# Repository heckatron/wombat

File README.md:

# wombat
Wireless sensor network using MQTT

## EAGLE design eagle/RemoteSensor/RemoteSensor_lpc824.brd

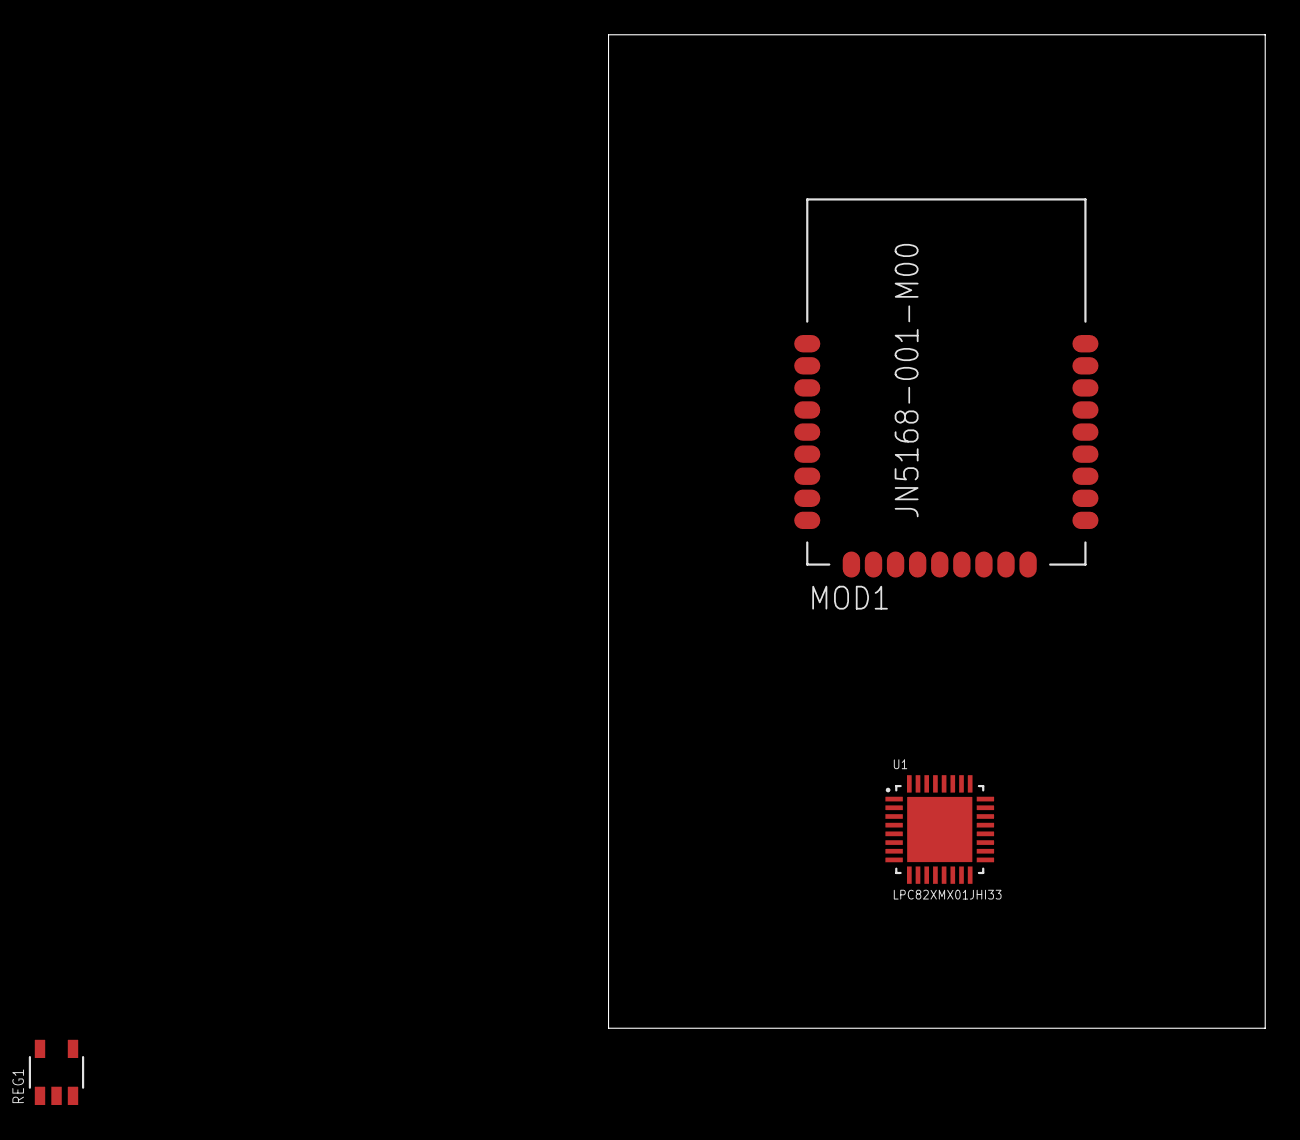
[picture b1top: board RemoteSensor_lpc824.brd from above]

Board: 2 copper layers, 37.8 x 57.1 mm, 3 parts (0 on the bottom side), 2 nets, no tracks yet.

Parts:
MOD1: JN5168-001-M00
REG1: LP3985DBV; SOT23
U1: LPC82XMX01JHI33; QFN33

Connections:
GND: MOD1.18, REG1.2
VDD: MOD1.17, U1.19

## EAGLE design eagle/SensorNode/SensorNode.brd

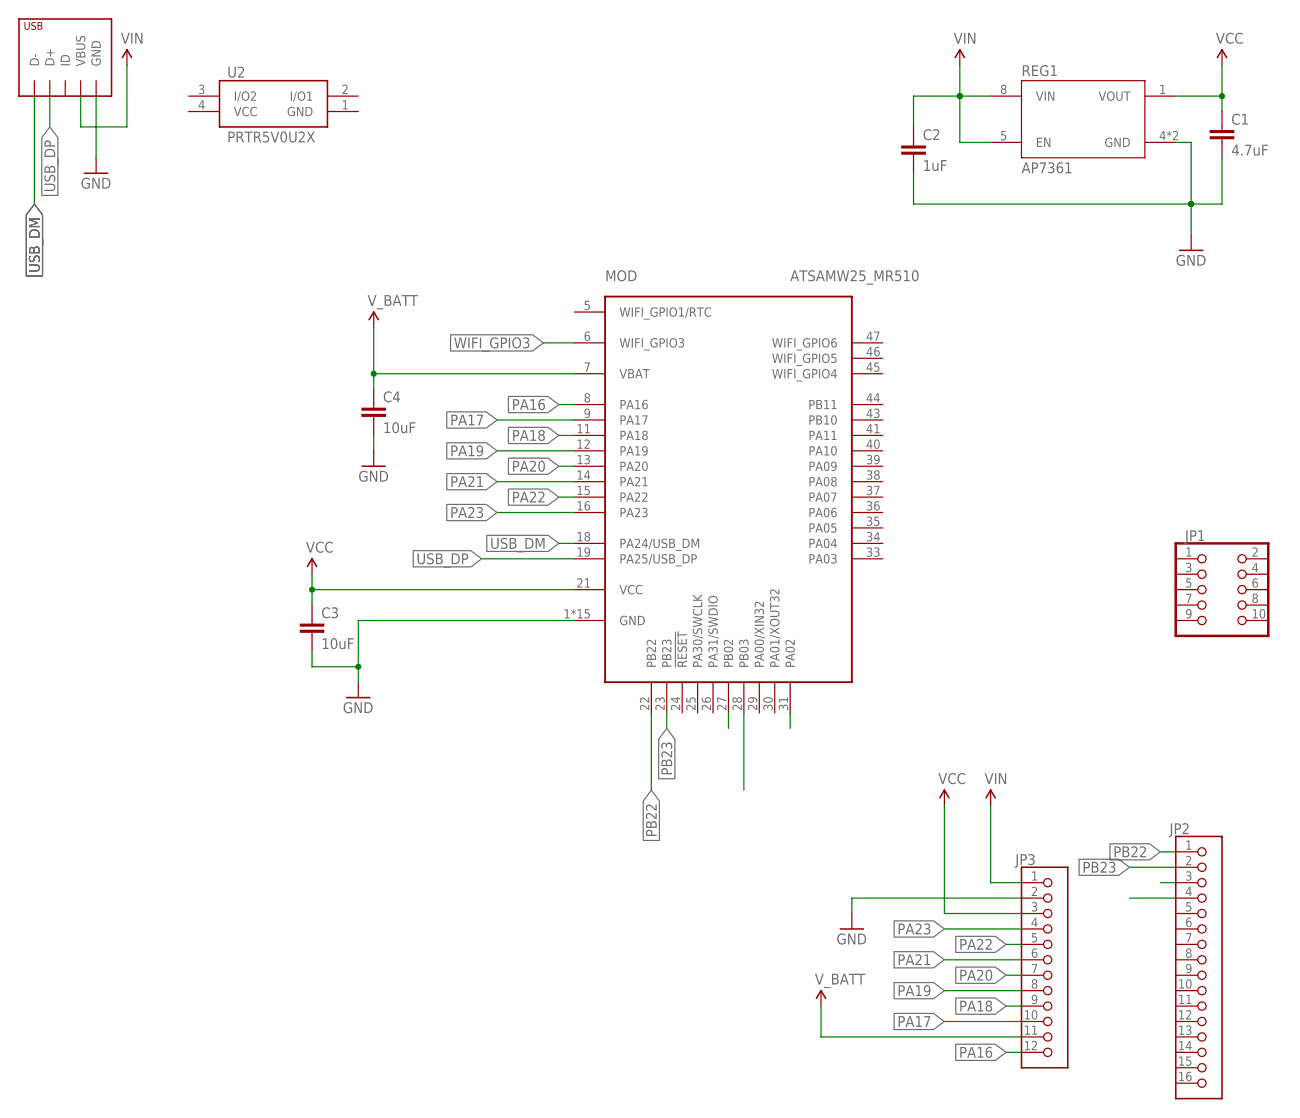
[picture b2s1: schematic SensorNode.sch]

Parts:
C1: 4.7uF; C0603
C2: 1uF; C0603
C3, C4: 10uF; C0603
JP1: HEADER_2X5MALE_PTH; HEADER_50MIL_2X5_PTH
JP2: HEADER_1X16; HEADER_100MIL_1X16
JP3: HEADER_1X12_100MIL; HEADER_100MIL_1X12
JP4: USB_RECEPTICLE_MICRO-B; USB_MICO_B
MOD: ATSAMW25_MR510; ATSAMW25
REG1: AP7361-FGE; UDFN-8
U2: PRTR5V0U2X; SOT143

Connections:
GND: C1.2, C2.2, C3.2, C4.2, JP3.2, JP4.GND, JP4.MOUNT$1 (GND), JP4.MOUNT$2 (GND), MOD.1 (GND), MOD.10 (GND), MOD.17 (GND), MOD.20 (GND), MOD.32 (GND), MOD.42 (GND), MOD.51 (GND), MOD.PAD$1 (GND), MOD.PAD$2 (GND), MOD.PAD$3 (GND), MOD.PAD$4 (GND), MOD.PAD$5 (GND), MOD.PAD$6 (GND), MOD.PAD$7 (GND), MOD.PAD$8 (GND), REG1.4 (GND), REG1.PAD (GND), U2.1 (GND)
PA02: MOD.31 (PA02)
PA16: JP3.12, MOD.8 (PA16)
PA17: JP3.10, MOD.9 (PA17)
PA18: JP3.9, MOD.11 (PA18)
PA19: JP3.8, MOD.12 (PA19)
PA20: JP3.7, MOD.13 (PA20)
PA21: JP3.6, MOD.14 (PA21)
PA22: JP3.5, MOD.15 (PA22)
PA23: JP3.4, MOD.16 (PA23)
PB02: MOD.27 (PB02)
PB03: MOD.28 (PB03)
PB22: JP2.1, MOD.22 (PB22)
PB23: JP2.2, MOD.23 (PB23)
USB_DM: JP4.D-, MOD.18 (PA24/USB_DM)
USB_DP: JP4.D+, MOD.19 (PA25/USB_DP)
VCC: C1.1, C3.1, JP3.3, MOD.21 (VCC), REG1.1 (VOUT), U2.4 (VCC)
VIN: C2.1, JP3.1, JP4.VBUS, REG1.5 (EN), REG1.8 (VIN)
V_BATT: C4.1, JP3.11, MOD.7 (VBAT)
WIFI_GPIO3: MOD.6 (WIFI_GPIO3)

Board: 2 copper layers, 11 parts (0 on the bottom side), 16 nets, no tracks yet.

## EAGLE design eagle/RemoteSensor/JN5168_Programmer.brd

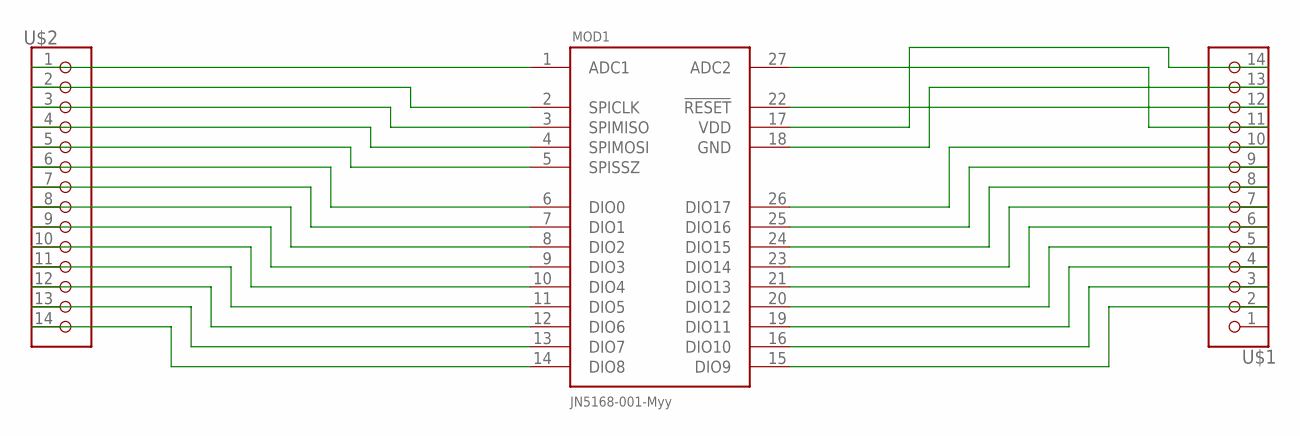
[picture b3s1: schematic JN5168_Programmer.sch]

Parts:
MOD1: JN5168-001-M00
U$1, U$2: HEADER_1X14_100MIL_PTH; HEADER_100MIL_1X14_PTH

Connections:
GND: MOD1.18 (GND), U$1.13
unnamed: MOD1.1 (ADC1), U$2.1
unnamed: MOD1.2 (SPICLK), U$2.2
unnamed: MOD1.3 (SPIMISO), U$2.3
unnamed: MOD1.4 (SPIMOSI), U$2.4
unnamed: MOD1.5 (SPISSZ), U$2.5
unnamed: MOD1.6 (DIO0), U$2.6
unnamed: MOD1.7 (DIO1), U$2.7
unnamed: MOD1.8 (DIO2), U$2.8
unnamed: MOD1.9 (DIO3), U$2.9
unnamed: MOD1.10 (DIO4), U$2.10
unnamed: MOD1.11 (DIO5), U$2.11
unnamed: MOD1.12 (DIO6), U$2.12
unnamed: MOD1.13 (DIO7), U$2.13
unnamed: MOD1.14 (DIO8), U$2.14
unnamed: MOD1.27 (ADC2), U$1.11
unnamed: MOD1.22 (!RESET), U$1.12
unnamed: MOD1.17 (VDD), U$1.14
unnamed: MOD1.26 (DIO17), U$1.10
unnamed: MOD1.25 (DIO16), U$1.9
unnamed: MOD1.24 (DIO15), U$1.8
unnamed: MOD1.23 (DIO14), U$1.7
unnamed: MOD1.21 (DIO13), U$1.6
unnamed: MOD1.20 (DIO12), U$1.5
unnamed: MOD1.19 (DIO11), U$1.4
unnamed: MOD1.16 (DIO10), U$1.3
unnamed: MOD1.15 (DIO9), U$1.2

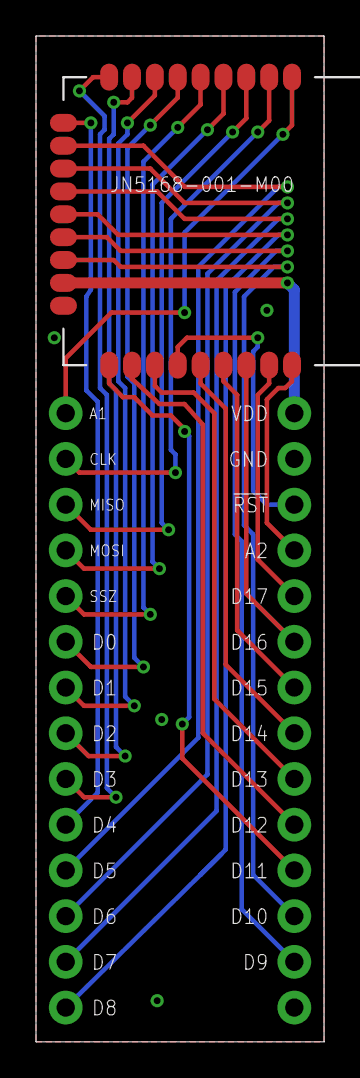
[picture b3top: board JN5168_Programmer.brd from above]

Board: 2 copper layers, 16.0 x 55.9 mm, 3 parts (0 on the bottom side), 27 nets.

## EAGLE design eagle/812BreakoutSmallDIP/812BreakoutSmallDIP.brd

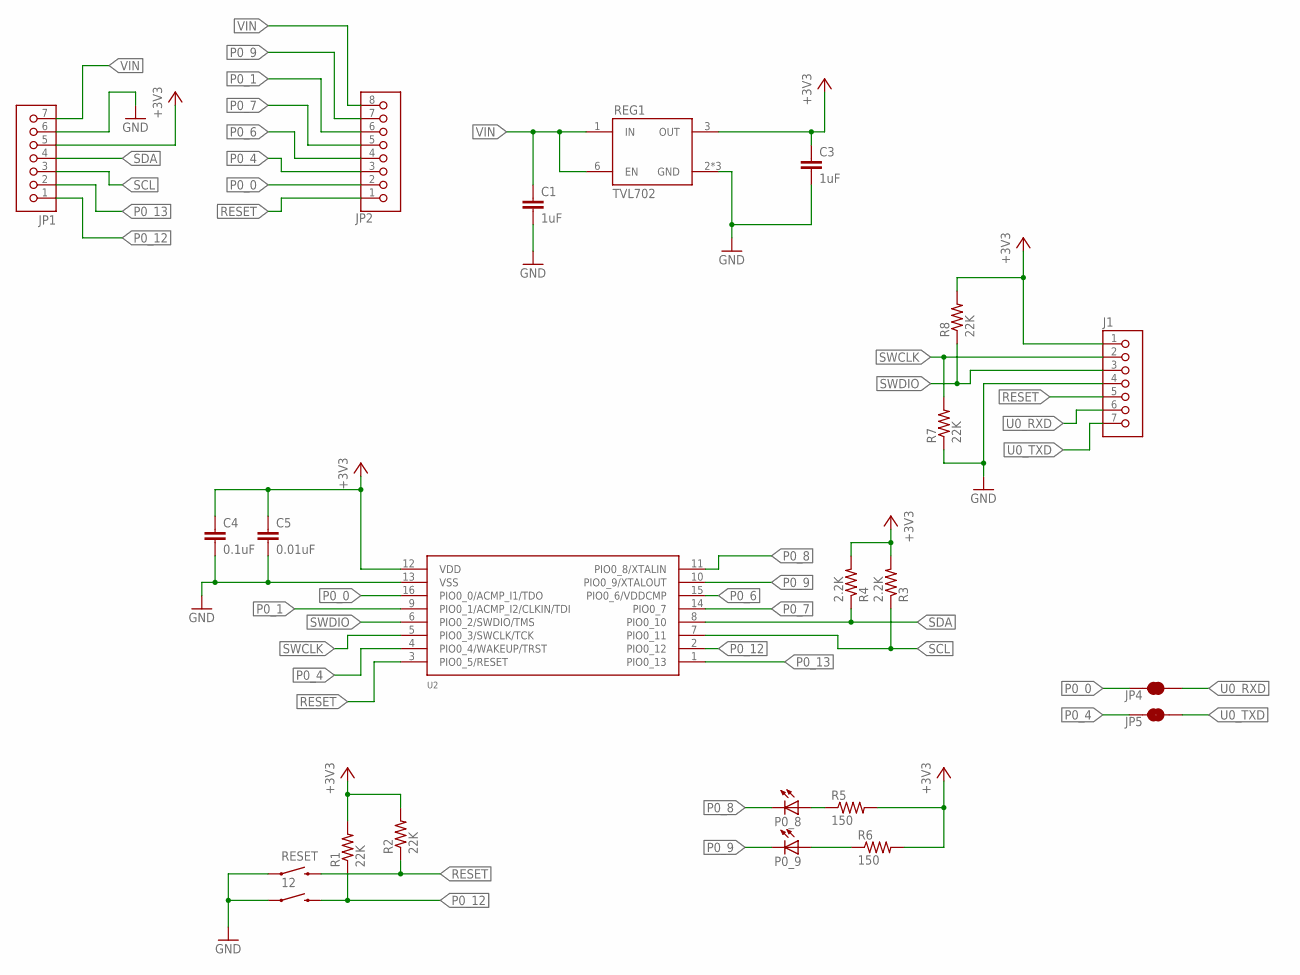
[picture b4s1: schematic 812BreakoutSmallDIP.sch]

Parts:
12: PTS820J15M; TACTILE_SWITCH_PTS820
C1, C3: 1uF; C0402
C4: 0.1uF; C0402
C5: 0.01uF; C0402
J1: HEADER_1X7_JST-SH_HORIZONTAL; JST-SH_HEADER_HORIZONTAL_7
JP1: HEADER_1X7_100MIL_PTH; HEADER_100MIL_1X7
JP2: HEADER_1X8_100MIL_PTH; HEADER_100MIL_1X8
JP4, JP5: JUMPER-PAD-2-NC_BY_TRACE; PAD-JUMPER-2-NC_BY_TRACE_YES_SILK
P0_8, P0_9: LEDCHIPLED_0603; CHIPLED_0603
R1, R2, R7, R8: 22K; R0402
R3, R4: 2.2K; R0402
R5, R6: 150; R0603
REG1: TVL702DSE; WSON-6
RESET: PTS820J15M; TACTILE_SWITCH_PTS820
U2: LPC812_16M101JTB16; SOT1341-1

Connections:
+3V3: C3.1, C4.1, C5.1, J1.1, JP1.5, R1.2, R2.2, R3.2, R4.2, R5.2, R6.2, R8.2, REG1.3 (OUT), U2.12 (VDD)
GND: 12.1, C1.2, C3.2, C4.2, C5.2, J1.4, JP1.6, R7.1, REG1.2 (GND), REG1.4 (GND), REG1.5 (GND), RESET.1, U2.13 (VSS)
unnamed: P0_9.A, R6.1
unnamed: P0_8.A, R5.1
P0_0: JP2.2, JP4.2, U2.16 (PIO0_0/ACMP_I1/TDO)
P0_1: JP2.6, U2.9 (PIO0_1/ACMP_I2/CLKIN/TDI)
P0_4: JP2.3, JP5.2, U2.4 (PIO0_4/WAKEUP/TRST)
P0_6: JP2.4, U2.15 (PIO0_6/VDDCMP)
P0_7: JP2.5, U2.14 (PIO0_7)
P0_8: P0_8.C, U2.11 (PIO0_8/XTALIN)
P0_9: JP2.7, P0_9.C, U2.10 (PIO0_9/XTALOUT)
P0_12: 12.2, JP1.1, R1.1, U2.2 (PIO0_12)
P0_13: JP1.2, U2.1 (PIO0_13)
RESET: J1.5, JP2.1, R2.1, RESET.2, U2.3 (PIO0_5/RESET)
SCL: JP1.3, R3.1, U2.7 (PIO0_11)
SDA: JP1.4, R4.1, U2.8 (PIO0_10)
SWCLK: J1.2, R7.2, U2.5 (PIO0_3/SWCLK/TCK)
SWDIO: J1.3, R8.1, U2.6 (PIO0_2/SWDIO/TMS)
U0_RXD: J1.6, JP4.1
U0_TXD: J1.7, JP5.1
VIN: C1.1, JP1.7, JP2.8, REG1.1 (IN), REG1.6 (EN)

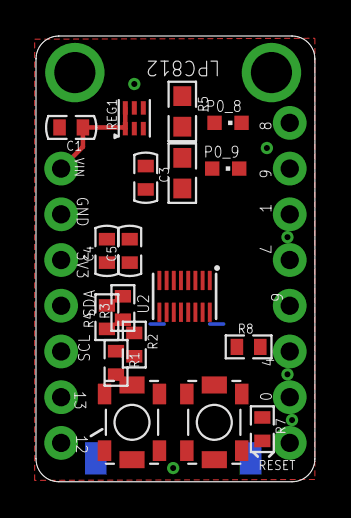
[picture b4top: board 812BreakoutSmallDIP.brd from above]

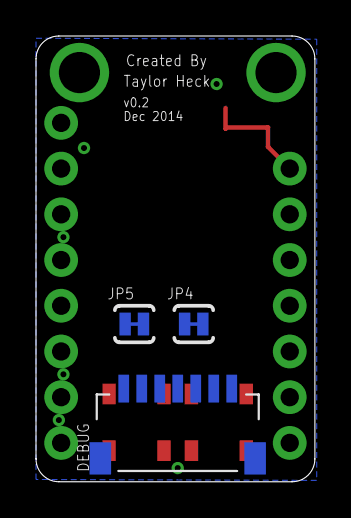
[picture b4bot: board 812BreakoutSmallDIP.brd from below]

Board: 2 copper layers, 15.5 x 24.8 mm, 23 parts (3 on the bottom side), 21 nets.

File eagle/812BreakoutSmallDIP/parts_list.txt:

812DIP	
Part	Value
	
12	PTS820J15M
C1	1uF
C2	0.01uF
C3	1uF
C4	0.1uF
C5	0.01uF
J1	HEADER_1X7_JST-SH_HORIZONTAL
JP3	HEADER_1X2JST-PH_HEADER_HORIZONTAL
P0_8	CHIPLED_0603
P0_9	CHIPLED_0603
R1	22K
R2	22K
R3	2.2K
R4	2.2K
R5	150
R6	150
R7	22K
R8	22K
RESET	PTS820J15M
U1	TPS73233DBVT
U2	LPC812_16M101JTB16

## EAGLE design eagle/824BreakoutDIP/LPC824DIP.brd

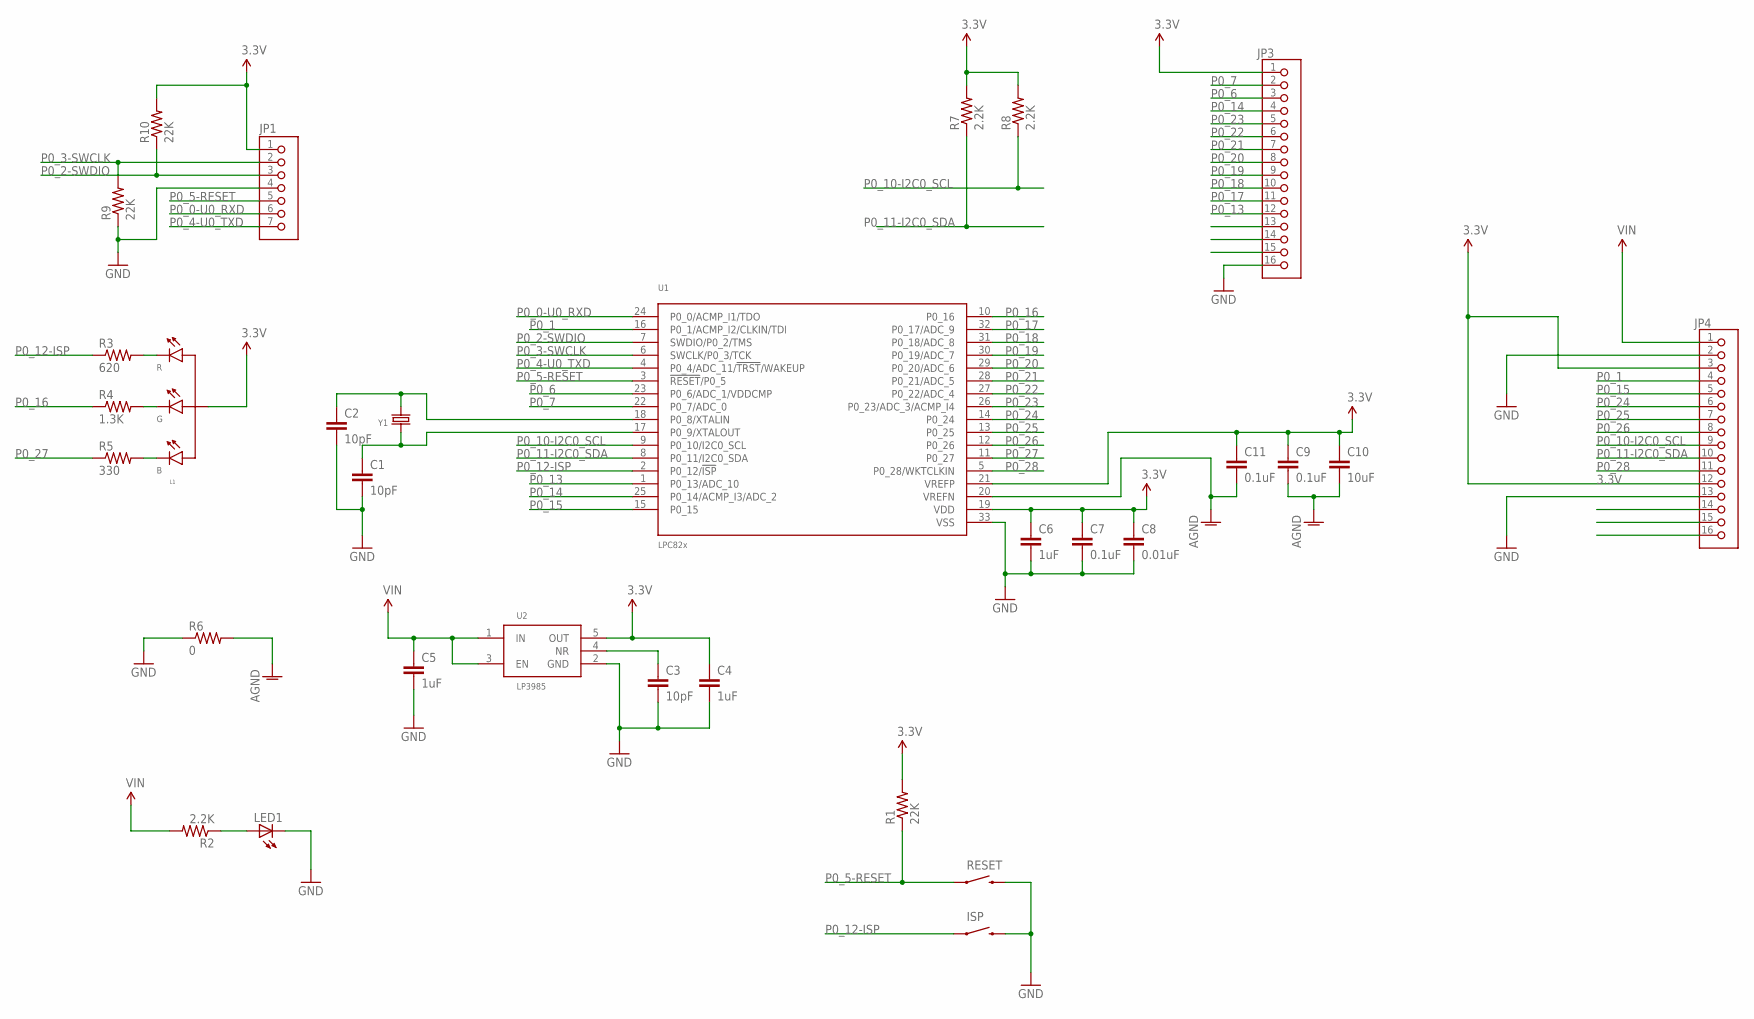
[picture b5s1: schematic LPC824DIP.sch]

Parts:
C1, C2, C3: 10pF; C0402
C4, C5, C6: 1uF; C0402
C7, C9, C11: 0.1uF; C0402
C8: 0.01uF; C0402
C10: 10uF; C0402
ISP: KMR221GLFS; TACTILE_SWITCH_SMD-3
JP1: HEADER_1X7_JST-SH_VERTICAL; JST-SH_HEADER_VERTICAL_7
JP3, JP4: HEADER_1X16; HEADER_100MIL_1X16
L1: LED_RGB_CA-CLVBA-FKA; P-LCC4-0
LED1: LEDCHIPLED_0603; CHIPLED_0603
R1, R9, R10: 22K; R0402
R2, R7, R8: 2.2K; R0402
R3: 620; R0402
R4: 1.3K; R0402
R5: 330; R0402
R6: 0; R0402
RESET: KMR221GLFS; TACTILE_SWITCH_SMD-3
U1: LPC82XMX01JHI33; QFN33
U2: LP3985DBV; SOT23
Y1: CRYSTAL_3.2X2.5_4PAD; CRYSTAL_SMD_3.2X2.5_4PAD

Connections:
3.3V: C4.1, C6.1, C7.1, C8.1, C9.1, C10.1, C11.1, JP1.1, JP3.1, JP4.3, JP4.12, L1.2 (A), R1.2, R7.2, R8.2, R10.2, U1.19 (VDD), U1.21 (VREFP), U2.5 (OUT)
AGND: C9.2, C10.2, C11.2, R6.2, U1.20 (VREFN)
GND: C1.2, C2.2, C3.2, C4.2, C5.2, C6.2, C7.2, C8.2, ISP.3 (2), ISP.4 (2), JP1.4, JP3.16, JP4.2, JP4.13, LED1.C, R6.1, R9.1, RESET.3 (2), RESET.4 (2), U1.33 (VSS), U2.2 (GND)
unnamed: C2.1, U1.18 (P0_8/XTALIN), Y1.3
unnamed: C1.1, U1.17 (P0_9/XTALOUT), Y1.1
unnamed: C3.1, U2.4 (NR)
unnamed: L1.1 (RK), R3.2
unnamed: LED1.A, R2.1
unnamed: L1.4 (GK), R4.2
unnamed: L1.3 (BK), R5.2
P0_0-U0_RXD: JP1.6, JP3.14, U1.24 (P0_0/ACMP_I1/TDO)
P0_1: JP4.4, U1.16 (P0_1/ACMP_I2/CLKIN/TDI)
P0_2-SWDIO: JP1.3, R10.1, U1.7 (SWDIO/P0_2/TMS)
P0_3-SWCLK: JP1.2, R9.2, U1.6 (SWCLK/P0_3/TCK)
P0_4-U0_TXD: JP1.7, JP3.13, U1.4 (P0_4/ADC_11/!TRST!/WAKEUP)
P0_5-RESET: JP1.5, JP4.14, R1.1, RESET.1, RESET.2 (1), U1.3 (!RESET!/P0_5)
P0_6: JP3.3, U1.23 (P0_6/ADC_1/VDDCMP)
P0_7: JP3.2, U1.22 (P0_7/ADC_0)
P0_10-I2C0_SCL: JP4.9, R8.1, U1.9 (P0_10/I2C0_SCL)
P0_11-I2C0_SDA: JP4.10, R7.1, U1.8 (P0_11/I2C0_SDA)
P0_12-ISP: ISP.1, ISP.2 (1), JP3.15, R3.1, U1.2 (P0_12/!ISP!)
P0_13: JP3.12, U1.1 (P0_13/ADC_10)
P0_14: JP3.4, U1.25 (P0_14/ACMP_I3/ADC_2)
P0_15: JP4.5, U1.15 (P0_15)
P0_16: JP4.16, R4.1, U1.10 (P0_16)
P0_17: JP3.11, U1.32 (P0_17/ADC_9)
P0_18: JP3.10, U1.31 (P0_18/ADC_8)
P0_19: JP3.9, U1.30 (P0_19/ADC_7)
P0_20: JP3.8, U1.29 (P0_20/ADC_6)
P0_21: JP3.7, U1.28 (P0_21/ADC_5)
P0_22: JP3.6, U1.27 (P0_22/ADC_4)
P0_23: JP3.5, U1.26 (P0_23/ADC_3/ACMP_I4)
P0_24: JP4.6, U1.14 (P0_24)
P0_25: JP4.7, U1.13 (P0_25)
P0_26: JP4.8, U1.12 (P0_26)
P0_27: JP4.15, R5.1, U1.11 (P0_27)
P0_28: JP4.11, U1.5 (P0_28/WKTCLKIN)
VIN: C5.1, JP4.1, R2.2, U2.1 (IN), U2.3 (EN)

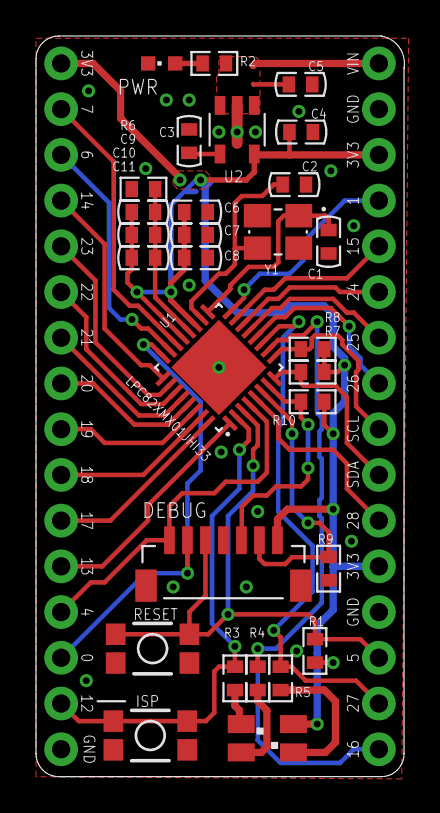
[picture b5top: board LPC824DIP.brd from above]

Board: 2 copper layers, 20.5 x 41.1 mm, 31 parts (0 on the bottom side), 38 nets.

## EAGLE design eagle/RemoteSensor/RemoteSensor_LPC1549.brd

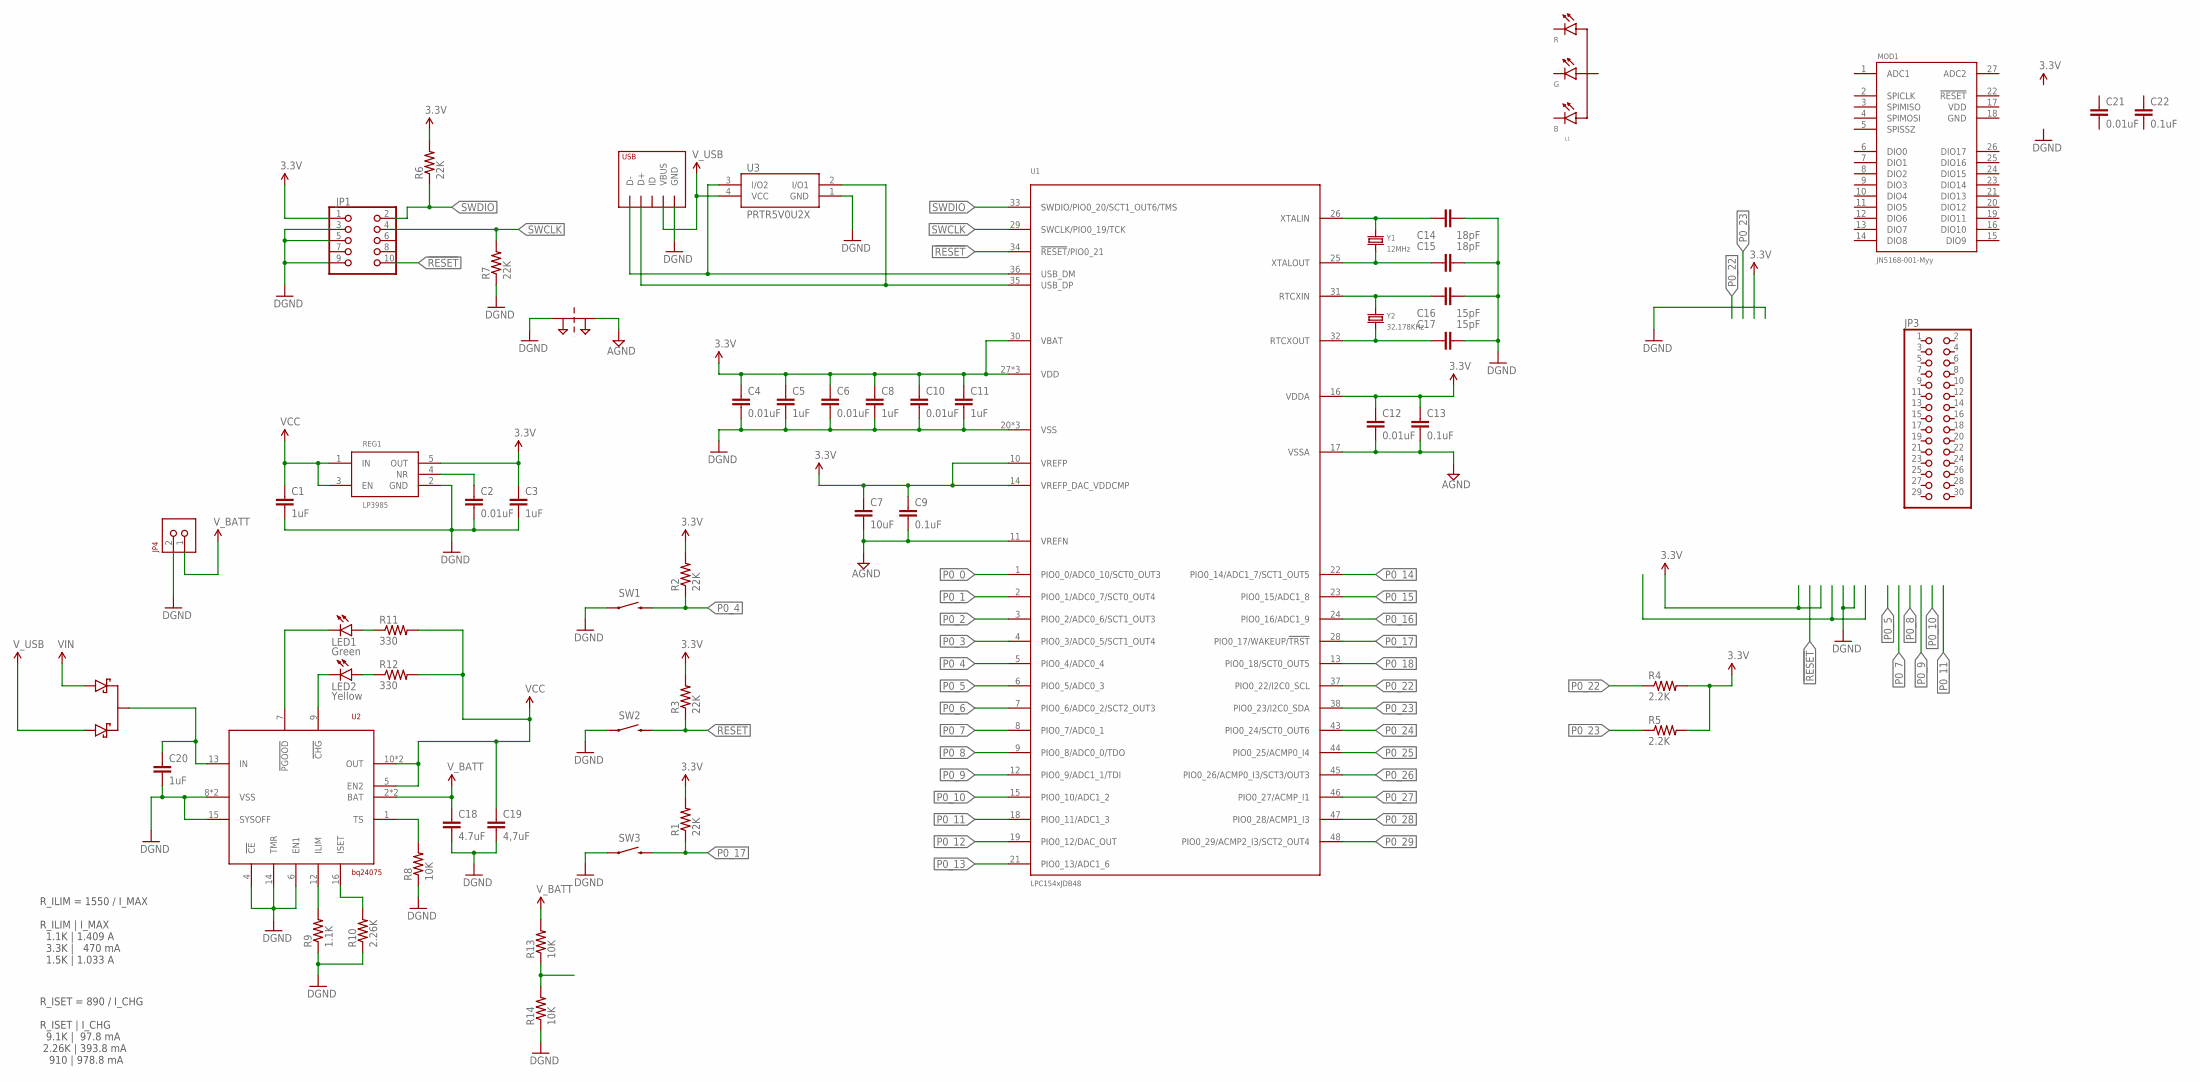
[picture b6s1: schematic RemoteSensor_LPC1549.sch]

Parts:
C1, C3, C5, C8, C11, C20: 1uF; C0603
C2, C4, C6, C10, C12, C21: 0.01uF; C0603
C7: 10uF; C0603
C9, C13, C22: 0.1uF; C0603
C14, C15: 18pF; C0603
C16, C17: 15pF; C0603
C18: 4.7uF; C0805
C19: 4,7uF; C0805
D1: DIODE_SCHOTTKY_DUAL_CMN_CATHODE_SOT1061; SOT1061
JP1: HEADER_2X5MALE_PTH; HEADER_50MIL_2X5_PTH
JP2: USB_RECEPTICLE_MICRO-B; USB_MICO_B
JP3: PINHD-2X15; 2X15
JP4: HEADER_1X2JST-PH_HEADER_HORIZONTAL; JST-PH-2-THM-RA
L1: LED_RGB_CA-CLVBA-FKA; P-LCC4-0
LED1: Green; LED-0603
LED2: Yellow; LED-0603
MOD1: JN5168-001-M00
PT1: 2PT_GND_TIE
R1, R2, R3, R6, R7: 22K; R0603
R4, R5: 2.2K; R0603
R8, R13, R14: 10K; R0603
R9: 1.1K; R0603
R10: 2.26K; R0603
R11, R12: 330; R0603
REG1: LP3985DBV; SOT23
SW1, SW2, SW3: KMR221GLFS; TACTILE_SWITCH_SMD-3
U1: LPC154XJDB48; TQFP48_7X7
U2: BQ24075; QFN16
U3: PRTR5V0U2X; SOT143
Y1: 12MHz; CRYSTAL_SMD_3.2X2.5_4PAD
Y2: 32.178KHz; CRYSTAL_3.2X1.5_2PAD

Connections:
3.3V: C3.1, C4.1, C5.1, C6.1, C7.1, C8.1, C9.1, C10.1, C11.1, C12.1, C13.1, JP1.1, R1.2, R2.2, R3.2, R4.2, R5.2, R6.2, REG1.5 (OUT), U1.10 (VREFP), U1.14 (VREFP_DAC_VDDCMP), U1.16 (VDDA), U1.27 (VDD), U1.30 (VBAT), U1.39 (VDD), U1.42 (VDD)
!RESET!: JP1.10, R3.1, SW2.3 (2), SW2.4 (2), U1.34 (!RESET!/PIO0_21)
AGND: C7.2, C9.2, C12.2, C13.2, PT1.P$2, U1.11 (VREFN), U1.17 (VSSA)
GND: C1.2, C2.2, C3.2, C4.2, C5.2, C6.2, C8.2, C10.2, C11.2, C14.2, C15.2, C16.2, C17.2, C18.2, C19.2, C20.2, JP1.3, JP1.5, JP1.9, JP2.GND, JP2.MOUNT$1 (GND), JP2.MOUNT$2 (GND), JP4.2 (1), MOD1.18 (GND), PT1.P$1, R7.1, R8.1, R9.1, R10.1, R14.1, REG1.2 (GND), SW1.1, SW1.2 (1), SW2.1, SW2.2 (1), SW3.1, SW3.2 (1), U1.20 (VSS), U1.40 (VSS), U1.41 (VSS), U2.4 (!CE), U2.6 (EN1), U2.8 (VSS), U2.14 (TMR), U2.15 (SYSOFF), U2.TH (VSS), U3.1 (GND)
unnamed: JP2.D+, U1.35 (USB_DP), U3.2 (I/O1)
unnamed: JP2.D-, U1.36 (USB_DM), U3.3 (I/O2)
unnamed: C14.1, U1.26 (XTALIN), Y1.1
unnamed: C15.1, U1.25 (XTALOUT), Y1.3
unnamed: C16.1, U1.31 (RTCXIN), Y2.P$1
unnamed: C17.1, U1.32 (RTCXOUT), Y2.P$2
unnamed: R9.2, U2.12 (ILIM)
unnamed: C2.1, REG1.4 (NR)
unnamed: R8.2, U2.1 (TS)
unnamed: LED1.A, R11.1
unnamed: R10.2, U2.16 (ISET)
unnamed: C20.1, D1.3 (K), U2.13 (IN)
unnamed: LED2.A, R12.1
unnamed: LED1.C, U2.7 (!PGOOD)
unnamed: LED2.C, U2.9 (!CHG)
P0_0: U1.1 (PIO0_0/ADC0_10/SCT0_OUT3)
P0_1: U1.2 (PIO0_1/ADC0_7/SCT0_OUT4)
P0_2: U1.3 (PIO0_2/ADC0_6/SCT1_OUT3)
P0_3: U1.4 (PIO0_3/ADC0_5/SCT1_OUT4)
P0_4: R2.1, SW1.3 (2), SW1.4 (2), U1.5 (PIO0_4/ADC0_4)
P0_5: R13.1, R14.2, U1.6 (PIO0_5/ADC0_3)
P0_6: U1.7 (PIO0_6/ADC0_2/SCT2_OUT3)
P0_7: U1.8 (PIO0_7/ADC0_1)
P0_8: U1.9 (PIO0_8/ADC0_0/TDO)
P0_9: U1.12 (PIO0_9/ADC1_1/TDI)
P0_10: U1.15 (PIO0_10/ADC1_2)
P0_11: U1.18 (PIO0_11/ADC1_3)
P0_12: U1.19 (PIO0_12/DAC_OUT)
P0_13: U1.21 (PIO0_13/ADC1_6)
P0_14: U1.22 (PIO0_14/ADC1_7/SCT1_OUT5)
P0_15: U1.23 (PIO0_15/ADC1_8)
P0_16: U1.24 (PIO0_16/ADC1_9)
P0_17: R1.1, SW3.3 (2), SW3.4 (2), U1.28 (PIO0_17/WAKEUP/!TRST!)
P0_18: U1.13 (PIO0_18/SCT0_OUT5)
P0_22: R4.1, U1.37 (PIO0_22/I2C0_SCL)
P0_23: R5.1, U1.38 (PIO0_23/I2C0_SDA)
P0_24: U1.43 (PIO0_24/SCT0_OUT6)
P0_25: U1.44 (PIO0_25/ACMP0_I4)
P0_26: U1.45 (PIO0_26/ACMP0_I3/SCT3/OUT3)
P0_27: U1.46 (PIO0_27/ACMP_I1)
P0_28: U1.47 (PIO0_28/ACMP1_I3)
P0_29: U1.48 (PIO0_29/ACMP2_I3/SCT2_OUT4)
SWCLK: JP1.4, R7.2, U1.29 (SWCLK/PIO0_19/TCK)
SWDIO: JP1.2, R6.1, U1.33 (SWDIO/PIO0_20/SCT1_OUT6/TMS)
VCC: C1.1, C19.1, R11.2, R12.2, REG1.1 (IN), REG1.3 (EN), U2.5 (EN2), U2.10 (OUT), U2.11 (OUT)
VDD: MOD1.17 (VDD)
VIN: D1.1 (A1)
V_BATT: C18.1, JP4.1 (2), R13.2, U2.2 (BAT), U2.3 (BAT)
V_USB: D1.2 (A2), JP2.VBUS, U3.4 (VCC)

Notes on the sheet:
R_ISET = 890 / I_CHG R_ISET | I_CHG 9.1K | 97.8 mA 2.26K | 393.8 mA 910 | 978.8 mA
R_ILIM = 1550 / I_MAX R_ILIM | I_MAX 1.1K | 1.409 A 3.3K | 470 mA 1.5K | 1.033 A

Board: 2 copper layers, 55 parts (0 on the bottom side), 29 nets, no tracks yet.

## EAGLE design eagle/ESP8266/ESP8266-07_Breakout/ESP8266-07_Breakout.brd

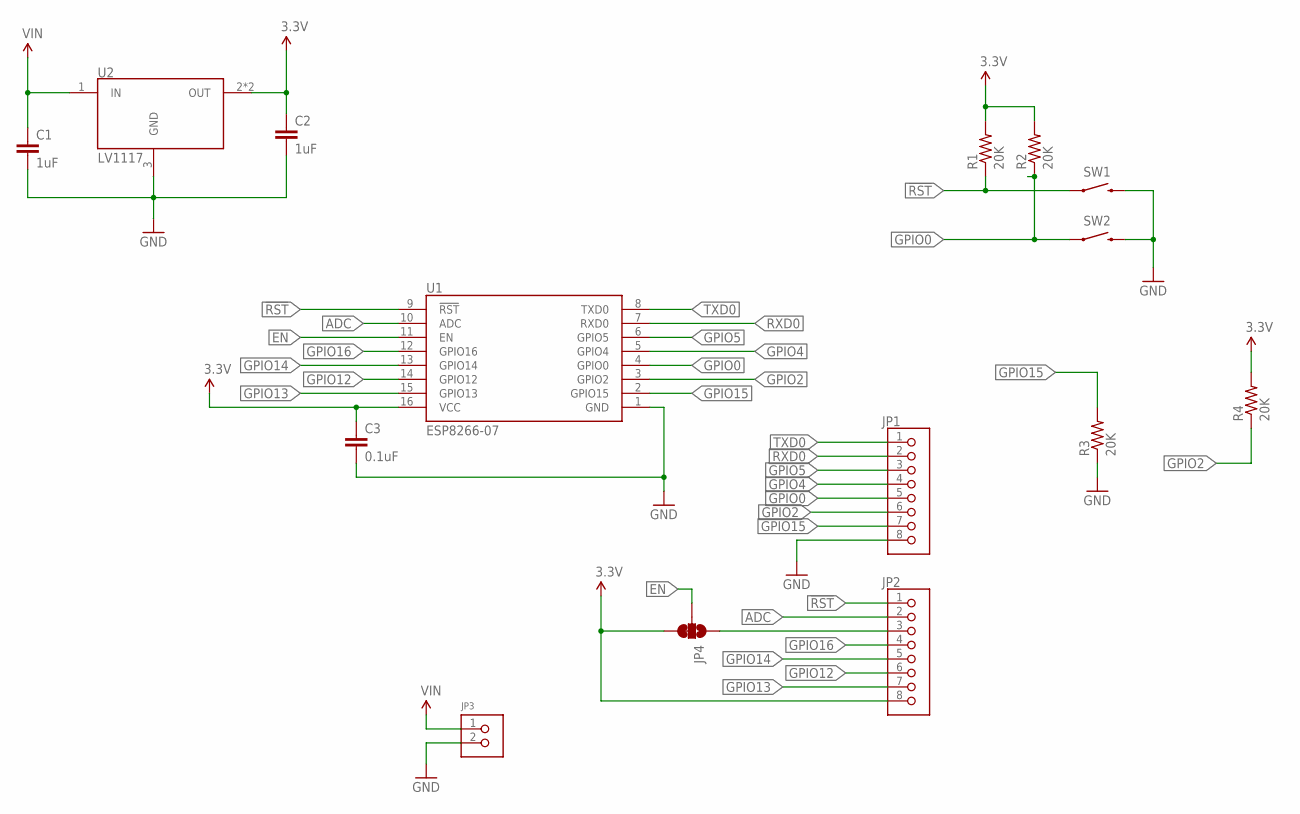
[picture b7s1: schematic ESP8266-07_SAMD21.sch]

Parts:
C1, C2: 1uF; C0603
C3: 0.1uF; C0603
JP1, JP2: HEADER_1X8_100MIL_PTH; HEADER_100MIL_1X8
JP3: HEADER_1X2_100MIL; HEADER_100MIL_1X2
JP4: JUMPER-PAD-3-2OF3_NC_BY_TRACE; PAD-JUMPER-3-2OF3_NC_BY_TRACE_YES_SILK_FULL_BOX
R1, R2, R3, R4: 20K; R0603
SW1, SW2: KMR221GLFS; TACTILE_SWITCH_SMD-3
U1: ESP8266-07
U2: TLV1114DCY; SOT223

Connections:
3.3V: C2.1, C3.1, JP2.8, JP4.3, R1.2, R2.2, R4.2, U1.16 (VCC), U2.2 (OUT), U2.TAB (OUT)
!RST: JP2.1, R1.1, SW1.1, SW1.2 (1), U1.9 (!RST)
ADC: JP2.2, U1.10 (ADC)
EN: JP4.2, U1.11 (EN)
GND: C1.2, C2.2, C3.2, JP1.8, JP3.2, R3.1, SW1.3 (2), SW1.4 (2), SW2.3 (2), SW2.4 (2), U1.1 (GND), U2.3 (GND)
GPIO0: JP1.5, R2.1, SW2.1, SW2.2 (1), U1.4 (GPIO0)
GPIO2: JP1.6, R4.1, U1.3 (GPIO2)
GPIO4: JP1.4, U1.5 (GPIO4)
GPIO5: JP1.3, U1.6 (GPIO5)
GPIO12: JP2.6, U1.14 (GPIO12)
GPIO13: JP2.7, U1.15 (GPIO13)
GPIO14: JP2.5, U1.13 (GPIO14)
GPIO15: JP1.7, R3.2, U1.2 (GPIO15)
GPIO16: JP2.4, U1.12 (GPIO16)
unnamed: JP2.3, JP4.1
RXD0: JP1.2, U1.7 (RXD0)
TXD0: JP1.1, U1.8 (TXD0)
VIN: C1.1, JP3.1, U2.1 (IN)

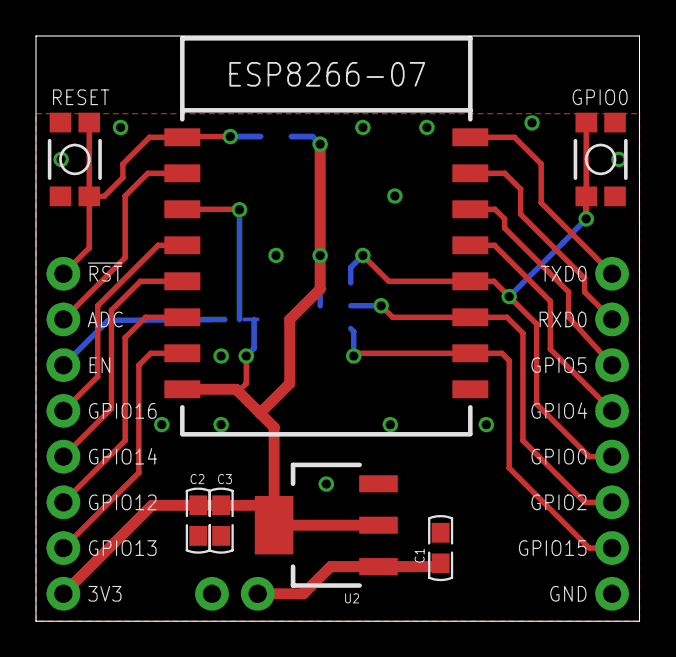
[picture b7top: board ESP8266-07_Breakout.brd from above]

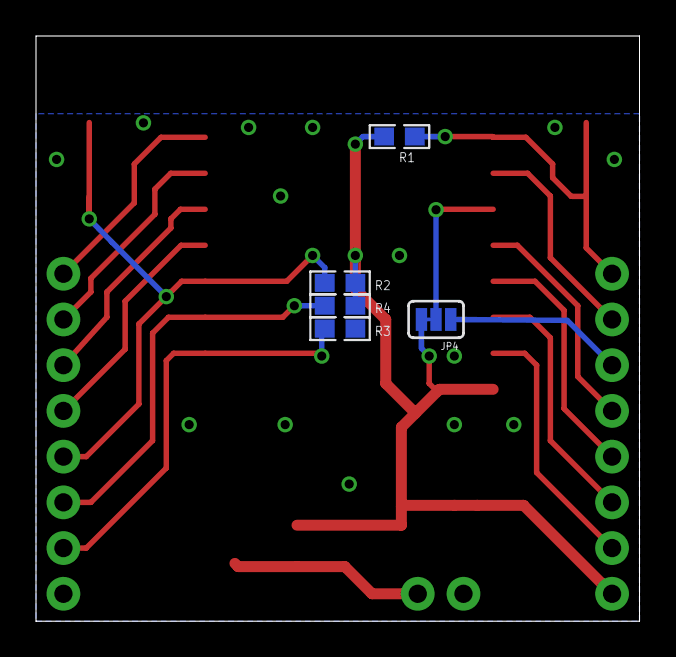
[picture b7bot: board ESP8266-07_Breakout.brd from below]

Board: 2 copper layers, 33.5 x 32.5 mm, 15 parts (5 on the bottom side), 18 nets.

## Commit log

2016-10-25 Initial commit
    Added ESP8266 and LPC812 code. Added eagle files.

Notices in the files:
parts and their libraries:
SparkFun-Passives: Licensing: Creative Commons ShareAlike 4.0 International - https://creativecommons.org/licenses/by-sa/4.0
